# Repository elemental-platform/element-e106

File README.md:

# element-e106
Wireless temperature, relative humidity and light sensor based on RFM69 radio

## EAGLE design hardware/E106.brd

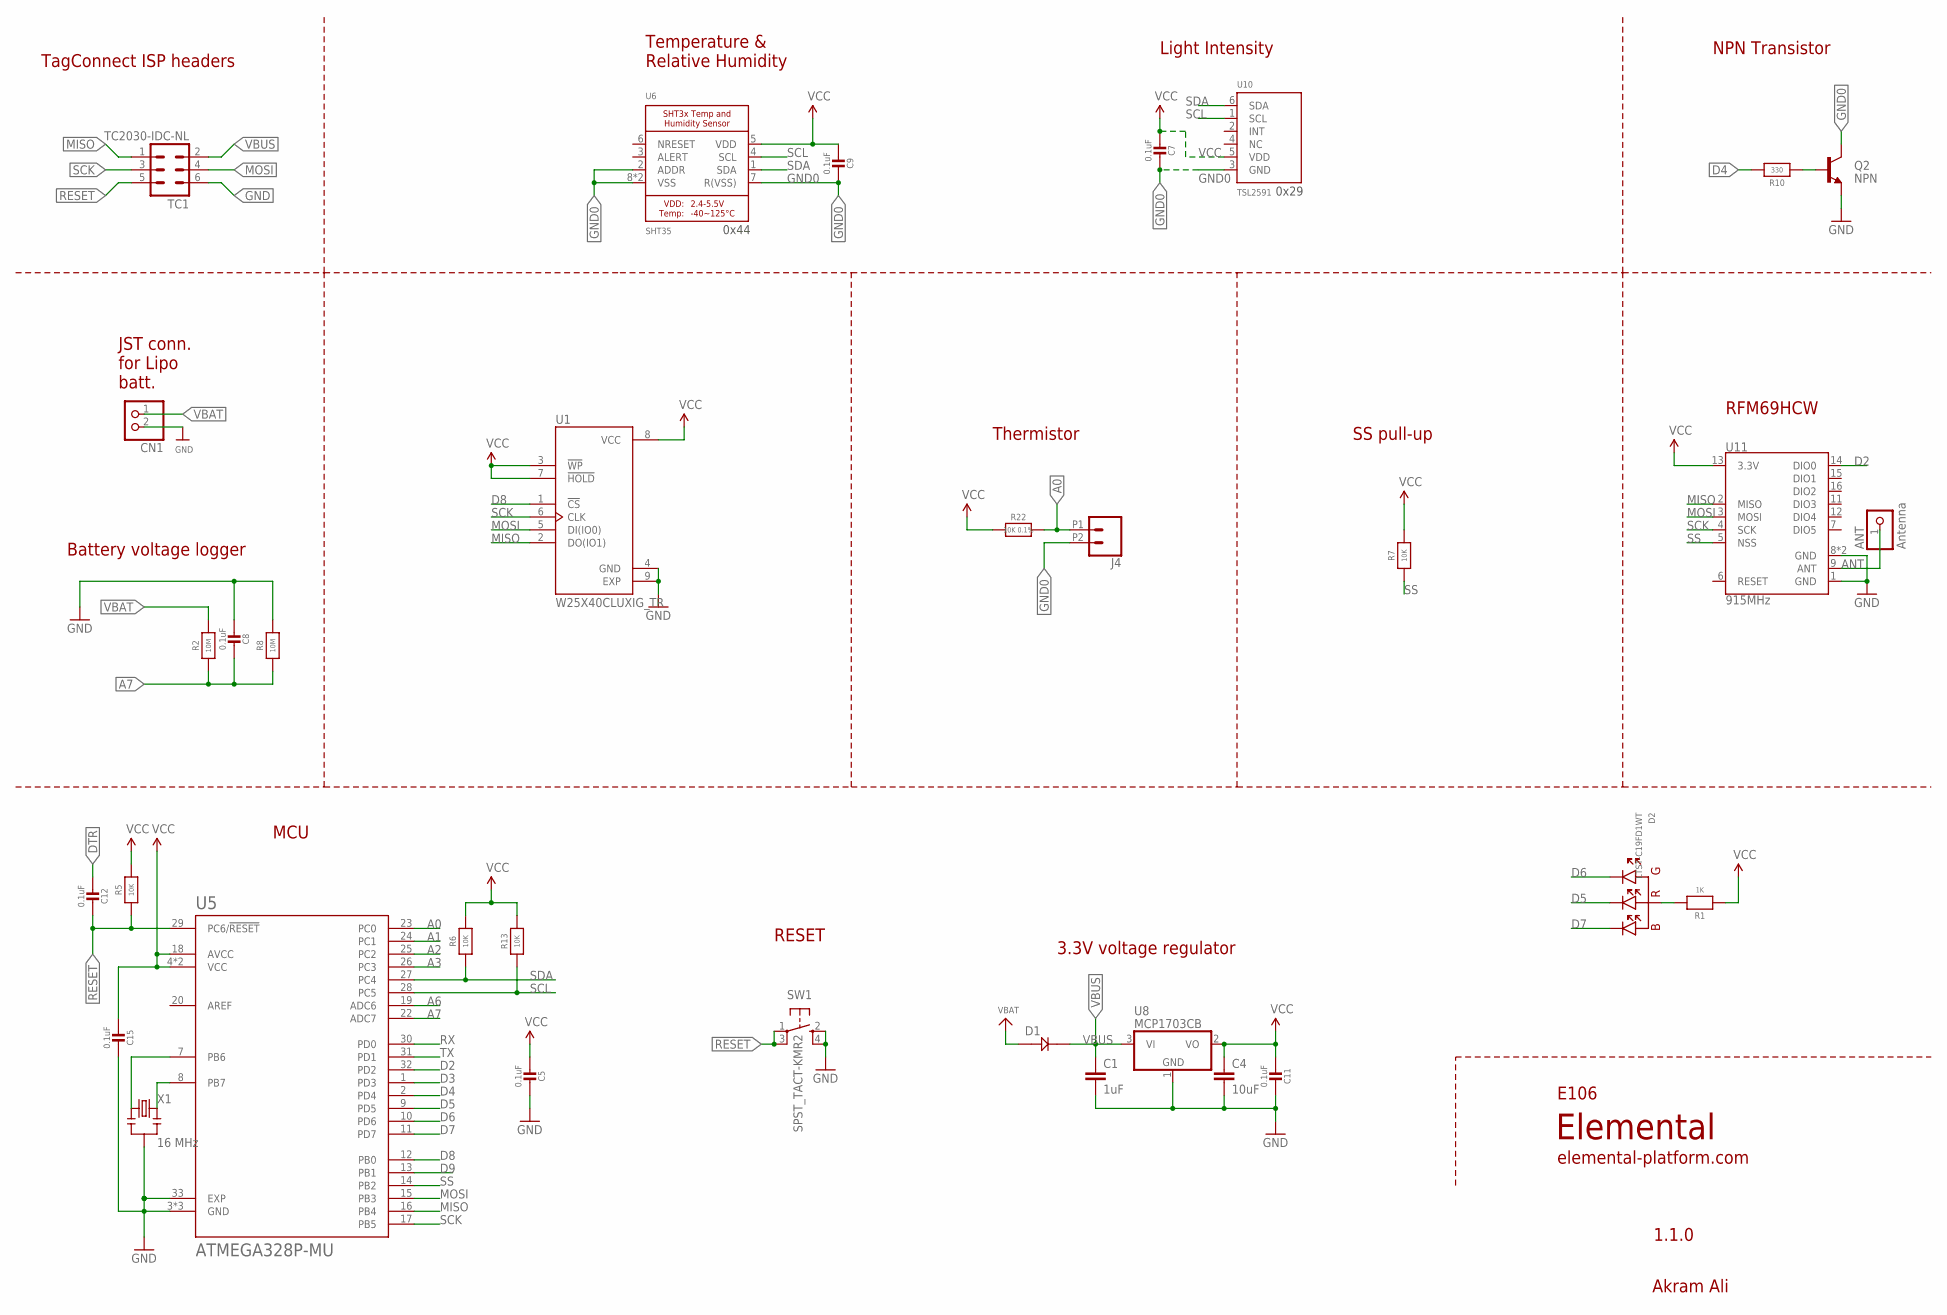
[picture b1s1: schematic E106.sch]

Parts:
ANT: Antenna; 1X01-CLEANBIG; MPN Helical antenna
C1: 1uF; 0805; MPN CC0805ZRY5V8BB105
C4: 10uF; 0805; MPN CC0805KKX5R6BB106
C5, C7, C8, C9, C11, C12, C15: 0.1uF; MICROBUILDER__0402MP; MPN GRM155R71C104KA88J
CN1: JST_2PIN-SMT-RA; JST-PH-2-SMT-RA
D1: DIODE_SCHOTTKY0805-RES; 0805
D2: LTST-C19FD1WT; 4-SMD
J4: CONN_022.54MM_SCREWTERM; 1X02_2.54_SCREWTERM
Q2: NPN; SOT23-3@1
R1: 1K; MICROBUILDER__0402MP; MPN RC0402JR-0710KL
R2, R8: 10M; MICROBUILDER__0402MP; MPN RC0402JR-0710KL
R5, R6, R7, R13: 10K; MICROBUILDER__0402MP; MPN RC0402JR-0710KL
R10: 330; MICROBUILDER__0402MP; MPN RC0402JR-0710KL
R22: 10K 0.1%; MICROBUILDER__0402MP; MPN RC0402JR-0727RL
SW1: SPST_TACT-KMR2; KMR2
TC1: TC2030-IDC-NL
U1: W25X40CLUXIG_TR; PSON50P300X200X60-9N
U5: ATMEGA328P-MU; QFN50P500X500X100-33N; MPN ATMEGA328P-MU
U6: SHT35; SHT3X; MPN SHT35-DIS-B
U8: MCP1703CB; SOT23; MPN MCP1703T-3302E/CB
U10: TSL2591; DFN6_TAOS; MPN TSL25911FN
U11: 915MHz; RFM69HCW-XXXS2; MPN RFM69HCW
X1: 16 MHz; RESONATOR-SMD; MPN CSTCE16M0V53-R0

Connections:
A0: J4.P1 (1), R22.2, U5.23 (PC0)
A1: U5.24 (PC1)
A2: U5.25 (PC2)
A3: U5.26 (PC3)
A6: U5.19 (ADC6)
A7: C8.1, R2.1, R8.1, U5.22 (ADC7)
ANT: ANT.1, U11.9 (ANT)
D2: U5.32 (PD2), U11.14 (DIO0)
D3: U5.1 (PD3)
D4: R10.2, U5.2 (PD4)
D5: D2.2 (C2), U5.9 (PD5)
D6: D2.3 (C3), U5.10 (PD6)
D7: D2.1 (C1), U5.11 (PD7)
D8: U1.1 (!CS), U5.12 (PB0)
D9: U5.13 (PB1)
DTR: C12.2
GND: C1.2, C4.2, C5.1, C8.2, C11.1, C15.1, CN1.2 (1), Q2.2 (E), R8.2, SW1.2 (S), SW1.4 (S1), TC1.6, U1.4 (GND), U1.9 (EXP), U5.3 (GND), U5.5 (GND), U5.21 (GND), U5.33 (EXP), U8.1 (GND), U11.1 (GND), U11.8 (GND), U11.10 (GND), X1.2
GND0: C7.1, C9.1, J4.P2 (2), Q2.3 (C), U6.2 (ADDR), U6.7 (R(VSS)), U6.8 (VSS), U6.THERMAL (VSS), U10.3 (GND)
MISO: TC1.1, U1.2 (DO(IO1)), U5.16 (PB4), U11.2 (MISO)
MOSI: TC1.4, U1.5 (DI(IO0)), U5.15 (PB3), U11.3 (MOSI)
unnamed: U5.8 (PB7), X1.3
unnamed: U5.7 (PB6), X1.1
unnamed: D2.4 (A), R1.2
unnamed: Q2.1 (B), R10.1
RESET: C12.1, R5.1, SW1.1, SW1.3 (P1), TC1.5, U5.29 (PC6/!RESET)
RX: U5.30 (PD0)
SCK: TC1.3, U1.6 (CLK), U5.17 (PB5), U11.4 (SCK)
SCL: R13.1, U5.28 (PC5), U6.4 (SCL), U10.1 (SCL)
SDA: R6.1, U5.27 (PC4), U6.1 (SDA), U10.6 (SDA)
SS: R7.1, U5.14 (PB2), U11.5 (NSS)
TX: U5.31 (PD1)
VBAT: CN1.1 (2), D1.1, R2.2
VBUS: C1.1, D1.2, TC1.2, U8.3 (VI)
VCC: C4.1, C5.2, C7.2, C9.2, C11.2, C15.2, R1.1, R5.2, R6.2, R7.2, R13.2, R22.1, U1.3 (!WP), U1.7 (!HOLD), U1.8 (VCC), U5.4 (VCC), U5.6 (VCC), U5.18 (AVCC), U6.5 (VDD), U8.2 (VO), U10.5 (VDD), U11.13 (3.3V)

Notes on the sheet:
Temperature & Relative Humidity
TagConnect ISP headers
3.3V voltage regulator
Elemental
E106
Akram Ali
1.1.0
elemental-platform.com
RFM69HCW
MCU
RESET
0x44
Battery voltage logger
NPN Transistor
JST conn. for Lipo batt.
Thermistor
SS pull-up
Light Intensity
0x29

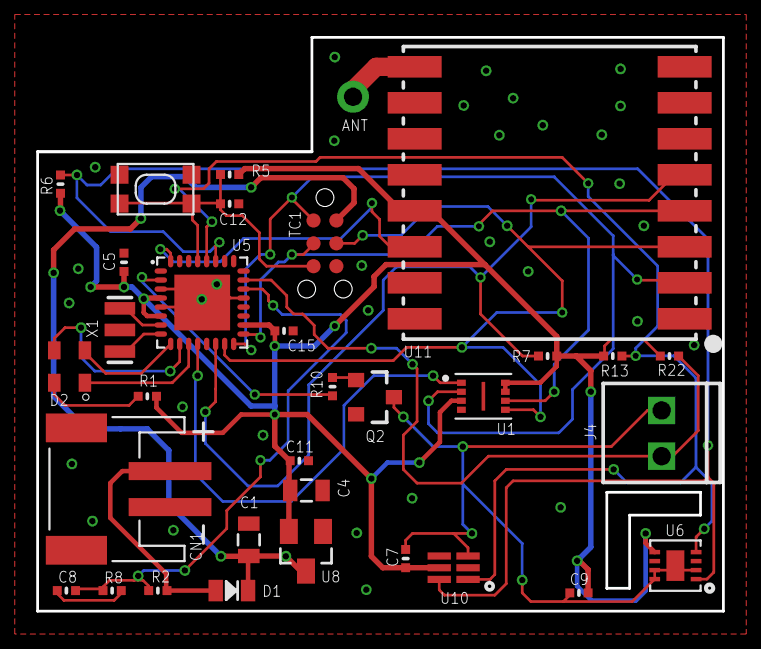
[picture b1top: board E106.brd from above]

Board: 2 copper layers, 38.1 x 31.9 mm, 33 parts (0 on the bottom side), 25 nets.

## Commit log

2019-09-02 Create LICENSE
2019-10-09 v1.1.0 - hardware update
    - added SPI flash
    - removed jumper from radio SS
    - added RGB LED instead of single LED
    - trace fixes
    - ERC/DRC
    - Silkscreen update
2019-10-17 minor adjustments
2019-10-17 added silkscreen for node id
2019-12-23 Update firmware.ino
    removed node ID from datapacket (gateway already has it in the encrypted packet, so it can retrieve it directly)
2019-12-23 Update firmware.ino
    small clean up
2019-12-23 Update firmware.ino
    added pin outputs
2020-01-23 v1.1.0
    - cleaned up code a lot
    - rearranged everything so it's much better ocntrolled now
    - can control RGB led and 16-bit with just one line now
    - added various ifdefs to control everything else, so no need to change everything except node parameters
2020-01-23 added upper limit to lux levels
    - just in case the value is too high, cap it at 90K
2020-01-23 minor bug fixes
    - fixed global variables to be in scope
    - reduced delays
    - rearranged code a bit more
    - compile check
2020-01-23 adjusted delays a bit
2020-01-23 major update
    - changed encryption key
2020-01-23 Update firmware.ino
    changed gateway packet to only send once without asking for acknowledgement so the "air" is clear and the node doesn't attemp sending multiple packets all the time
2020-01-29 changed default freq. to 905mhz
2020-02-04 added control node check
    - Defined control node. If not available, just uncomment HAS_CONTROL_NODE. The code should take care of the rest.

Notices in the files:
parts and their libraries:
SparkFun-Capacitors: Licensing: Creative Commons ShareAlike 4.0 International - https://creativecommons.org/licenses/by-sa/4.0
microbuilder: This work is placed in the public domain, and may be freely used for commercial and non-commercial work with the following conditions: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
